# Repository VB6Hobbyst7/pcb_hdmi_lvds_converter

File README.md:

# pcb_hdmi_lvds_converter
Design files for a pcb to convert HDMI to LVDS, based on the chalkboard design.

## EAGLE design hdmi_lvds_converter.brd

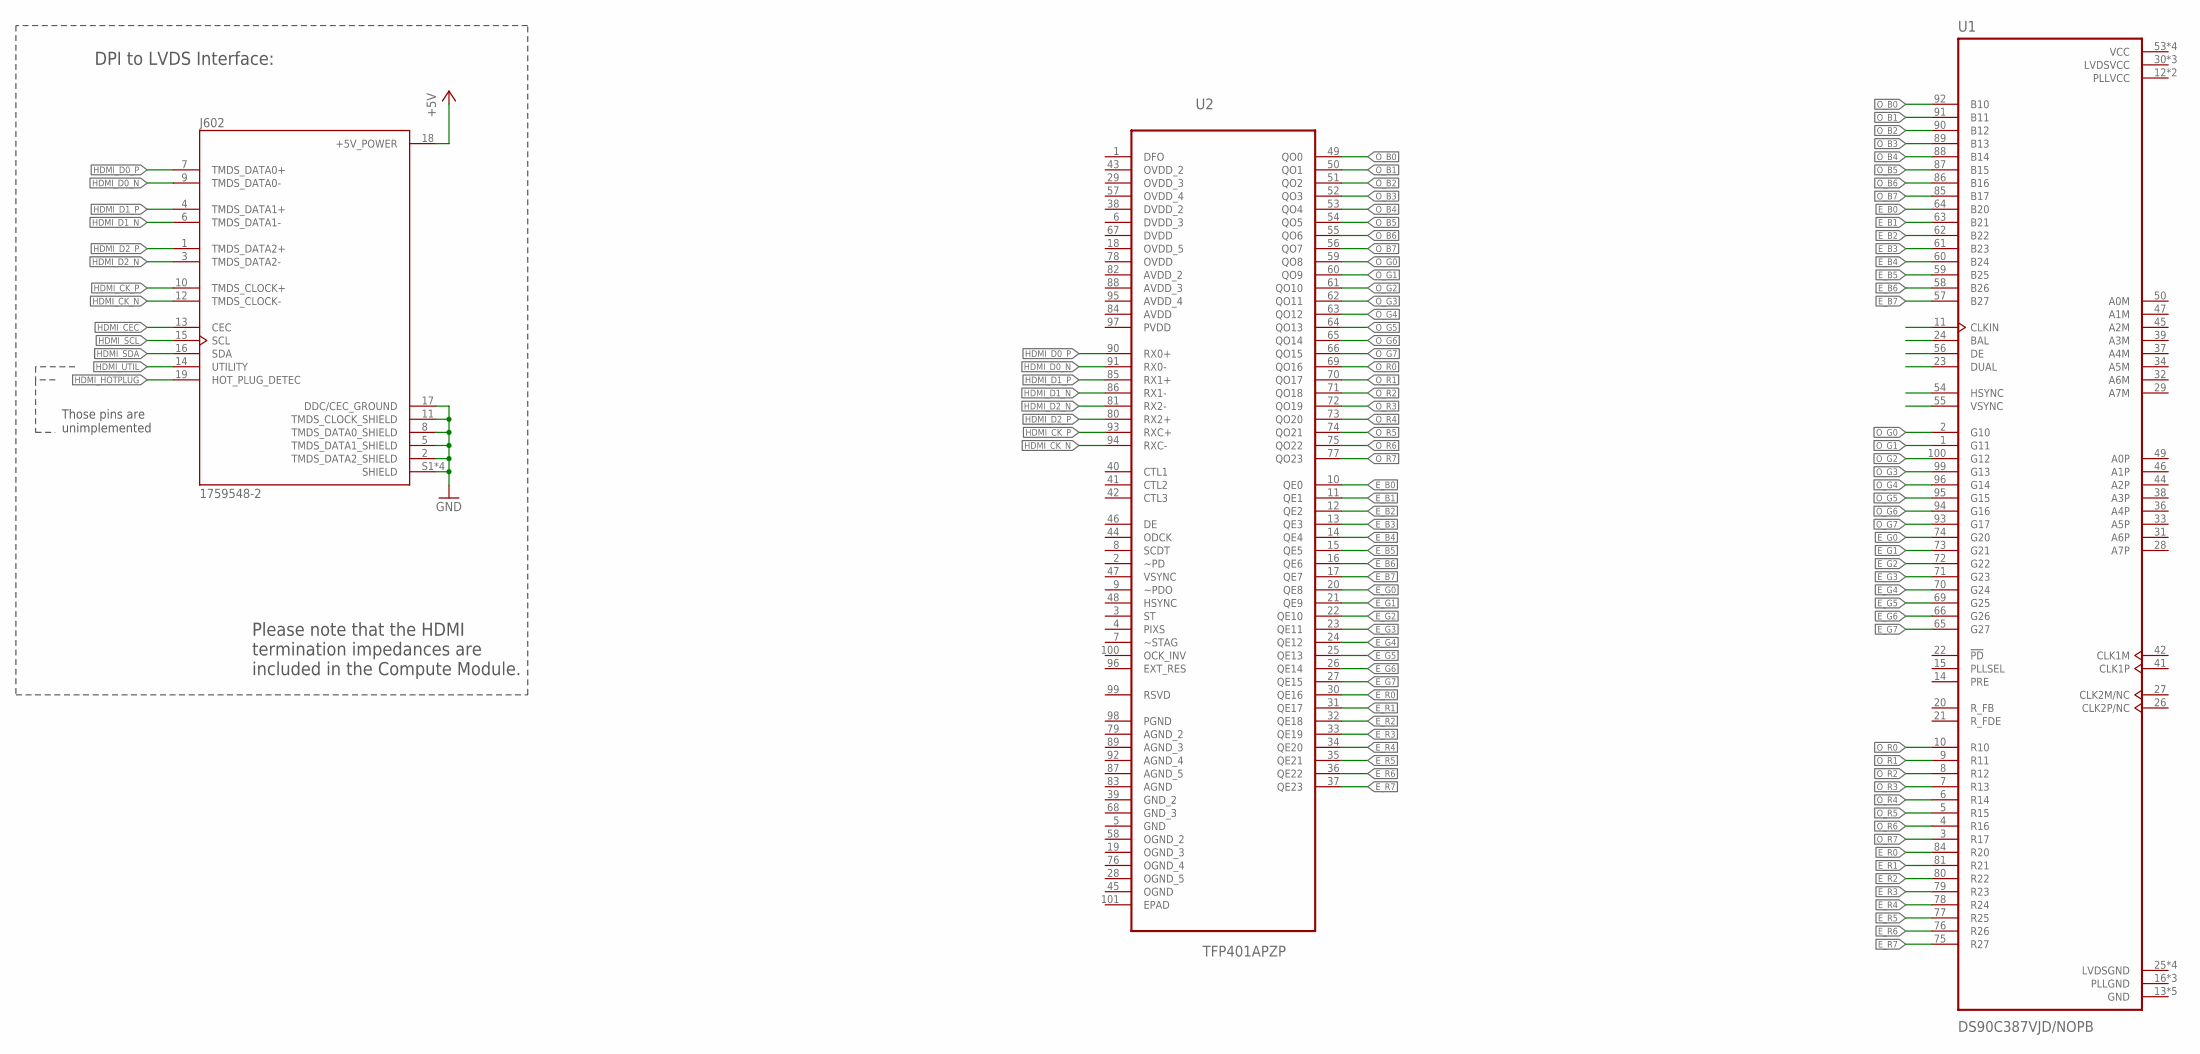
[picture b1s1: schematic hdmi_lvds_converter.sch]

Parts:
J602: 1759548-2; TE_1759548-2
U1: DS90C387VJD/NOPB; QFP50P1600X1600X120-100N
U2: TFP401APZP; QFP50P1600X1600X120-101N

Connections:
+5V: J602.18 (+5V_POWER)
AVDD: U2.84 (AVDD)
AVDD_2: U2.82 (AVDD_2)
AVDD_3: U2.88 (AVDD_3)
AVDD_4: U2.95 (AVDD_4)
DVDD: U2.67 (DVDD)
DVDD_2: U2.38 (DVDD_2)
DVDD_3: U2.6 (DVDD_3)
E_B0: U1.64 (B20), U2.10 (QE0)
E_B1: U1.63 (B21), U2.11 (QE1)
E_B2: U1.62 (B22), U2.12 (QE2)
E_B3: U1.61 (B23), U2.13 (QE3)
E_B4: U1.60 (B24), U2.14 (QE4)
E_B5: U1.59 (B25), U2.15 (QE5)
E_B6: U1.58 (B26), U2.16 (QE6)
E_B7: U1.57 (B27), U2.17 (QE7)
E_G0: U1.74 (G20), U2.20 (QE8)
E_G1: U1.73 (G21), U2.21 (QE9)
E_G2: U1.72 (G22), U2.22 (QE10)
E_G3: U1.71 (G23), U2.23 (QE11)
E_G4: U1.70 (G24), U2.24 (QE12)
E_G5: U1.69 (G25), U2.25 (QE13)
E_G6: U1.66 (G26), U2.26 (QE14)
E_G7: U1.65 (G27), U2.27 (QE15)
E_R0: U1.84 (R20), U2.30 (QE16)
E_R1: U1.81 (R21), U2.31 (QE17)
E_R2: U1.80 (R22), U2.32 (QE18)
E_R3: U1.79 (R23), U2.33 (QE19)
E_R4: U1.78 (R24), U2.34 (QE20)
E_R5: U1.77 (R25), U2.35 (QE21)
E_R6: U1.76 (R26), U2.36 (QE22)
E_R7: U1.75 (R27), U2.37 (QE23)
GND: J602.2 (TMDS_DATA2_SHIELD), J602.5 (TMDS_DATA1_SHIELD), J602.8 (TMDS_DATA0_SHIELD), J602.11 (TMDS_CLOCK_SHIELD), J602.17 (DDC/CEC_GROUND), J602.S1 (SHIELD), J602.S2 (SHIELD), J602.S3 (SHIELD), J602.S4 (SHIELD), U1.13 (GND), U1.52 (GND), U1.68 (GND), U1.83 (GND), U1.98 (GND)
HDMI_CEC: J602.13 (CEC)
HDMI_CK_N: J602.12 (TMDS_CLOCK-), U2.94 (RXC-)
HDMI_CK_P: J602.10 (TMDS_CLOCK+), U2.93 (RXC+)
HDMI_D0_N: J602.9 (TMDS_DATA0-), U2.91 (RX0-)
HDMI_D0_P: J602.7 (TMDS_DATA0+), U2.90 (RX0+)
HDMI_D1_N: J602.6 (TMDS_DATA1-), U2.86 (RX1-)
HDMI_D1_P: J602.4 (TMDS_DATA1+), U2.85 (RX1+)
HDMI_D2_N: J602.3 (TMDS_DATA2-), U2.81 (RX2-)
HDMI_D2_P: J602.1 (TMDS_DATA2+), U2.80 (RX2+)
HDMI_HOTPLUG: J602.19 (HOT_PLUG_DETEC)
HDMI_SCL: J602.15 (SCL)
HDMI_SDA: J602.16 (SDA)
HDMI_UTIL: J602.14 (UTILITY)
LVDSGND: U1.25 (LVDSGND), U1.35 (LVDSGND), U1.43 (LVDSGND), U1.51 (LVDSGND)
OVDD: U2.78 (OVDD)
OVDD_2: U2.43 (OVDD_2)
OVDD_3: U2.29 (OVDD_3)
OVDD_4: U2.57 (OVDD_4)
OVDD_5: U2.18 (OVDD_5)
O_B0: U1.92 (B10), U2.49 (QO0)
O_B1: U1.91 (B11), U2.50 (QO1)
O_B2: U1.90 (B12), U2.51 (QO2)
O_B3: U1.89 (B13), U2.52 (QO3)
O_B4: U1.88 (B14), U2.53 (QO4)
O_B5: U1.87 (B15), U2.54 (QO5)
O_B6: U1.86 (B16), U2.55 (QO6)
O_B7: U1.85 (B17), U2.56 (QO7)
O_G0: U1.2 (G10), U2.59 (QO8)
O_G1: U1.1 (G11), U2.60 (QO9)
O_G2: U1.100 (G12), U2.61 (QO10)
O_G3: U1.99 (G13), U2.62 (QO11)
O_G4: U1.96 (G14), U2.63 (QO12)
O_G5: U1.95 (G15), U2.64 (QO13)
O_G6: U1.94 (G16), U2.65 (QO14)
O_G7: U1.93 (G17), U2.66 (QO15)
O_R0: U1.10 (R10), U2.69 (QO16)
O_R1: U1.9 (R11), U2.70 (QO17)
O_R2: U1.8 (R12), U2.71 (QO18)
O_R3: U1.7 (R13), U2.72 (QO19)
O_R4: U1.6 (R14), U2.73 (QO20)
O_R5: U1.5 (R15), U2.74 (QO21)
O_R6: U1.4 (R16), U2.75 (QO22)
O_R7: U1.3 (R17), U2.77 (QO23)
PLLGND: U1.16 (PLLGND), U1.17 (PLLGND), U1.19 (PLLGND)
PLLVCC: U1.12 (PLLVCC), U1.18 (PLLVCC)
PVDD: U2.97 (PVDD)
VCC: U1.53 (VCC), U1.67 (VCC), U1.82 (VCC), U1.97 (VCC)

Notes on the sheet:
DPI to LVDS Interface:
Please note that the HDMI termination impedances are included in the Compute Module.
Those pins are unimplemented

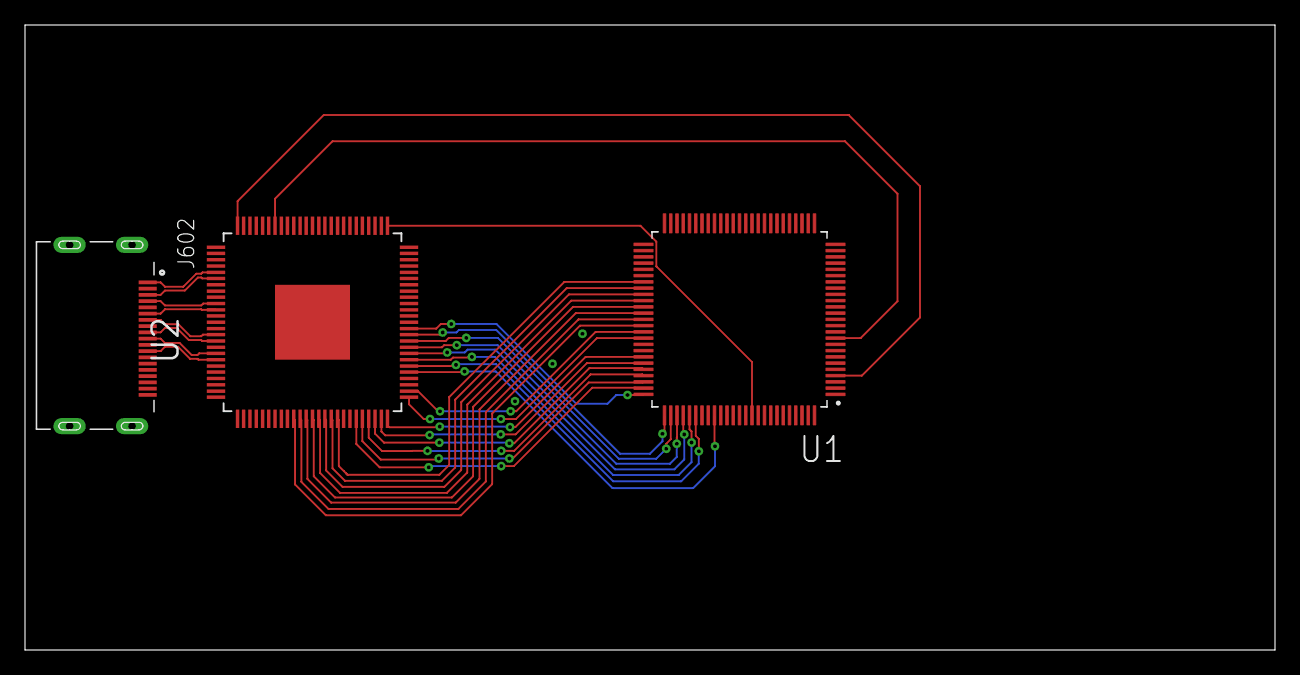
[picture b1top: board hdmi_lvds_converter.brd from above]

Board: 4 copper layers, 100.0 x 50.0 mm, 3 parts (0 on the bottom side), 61 nets.

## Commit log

2020-06-12 - Create Schematic and Bpard files. - Add the main parts required for the converter.
2020-06-12 - Change HDMI connector for better layout. - Start routing rgb signals.
2020-06-12 - Start routing LVDS lines.
2020-06-12 - Latest changes
